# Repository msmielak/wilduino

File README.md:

# wilduino
Arduino-based, open-source animal-borne logger

Copyright (C) 2016  Michał Śmielak

    This program is free software: you can redistribute it and/or modify
    it under the terms of the GNU General Public License as published by
    the Free Software Foundation, either version 3 of the License, or
    (at your option) any later version.

    This program is distributed in the hope that it will be useful,
    but WITHOUT ANY WARRANTY; without even the implied warranty of
    MERCHANTABILITY or FITNESS FOR A PARTICULAR PURPOSE.  See the
    GNU General Public License for more details.

    You should have received a copy of the GNU General Public License
    along with this program.  If not, see <http://www.gnu.org/licenses/>.

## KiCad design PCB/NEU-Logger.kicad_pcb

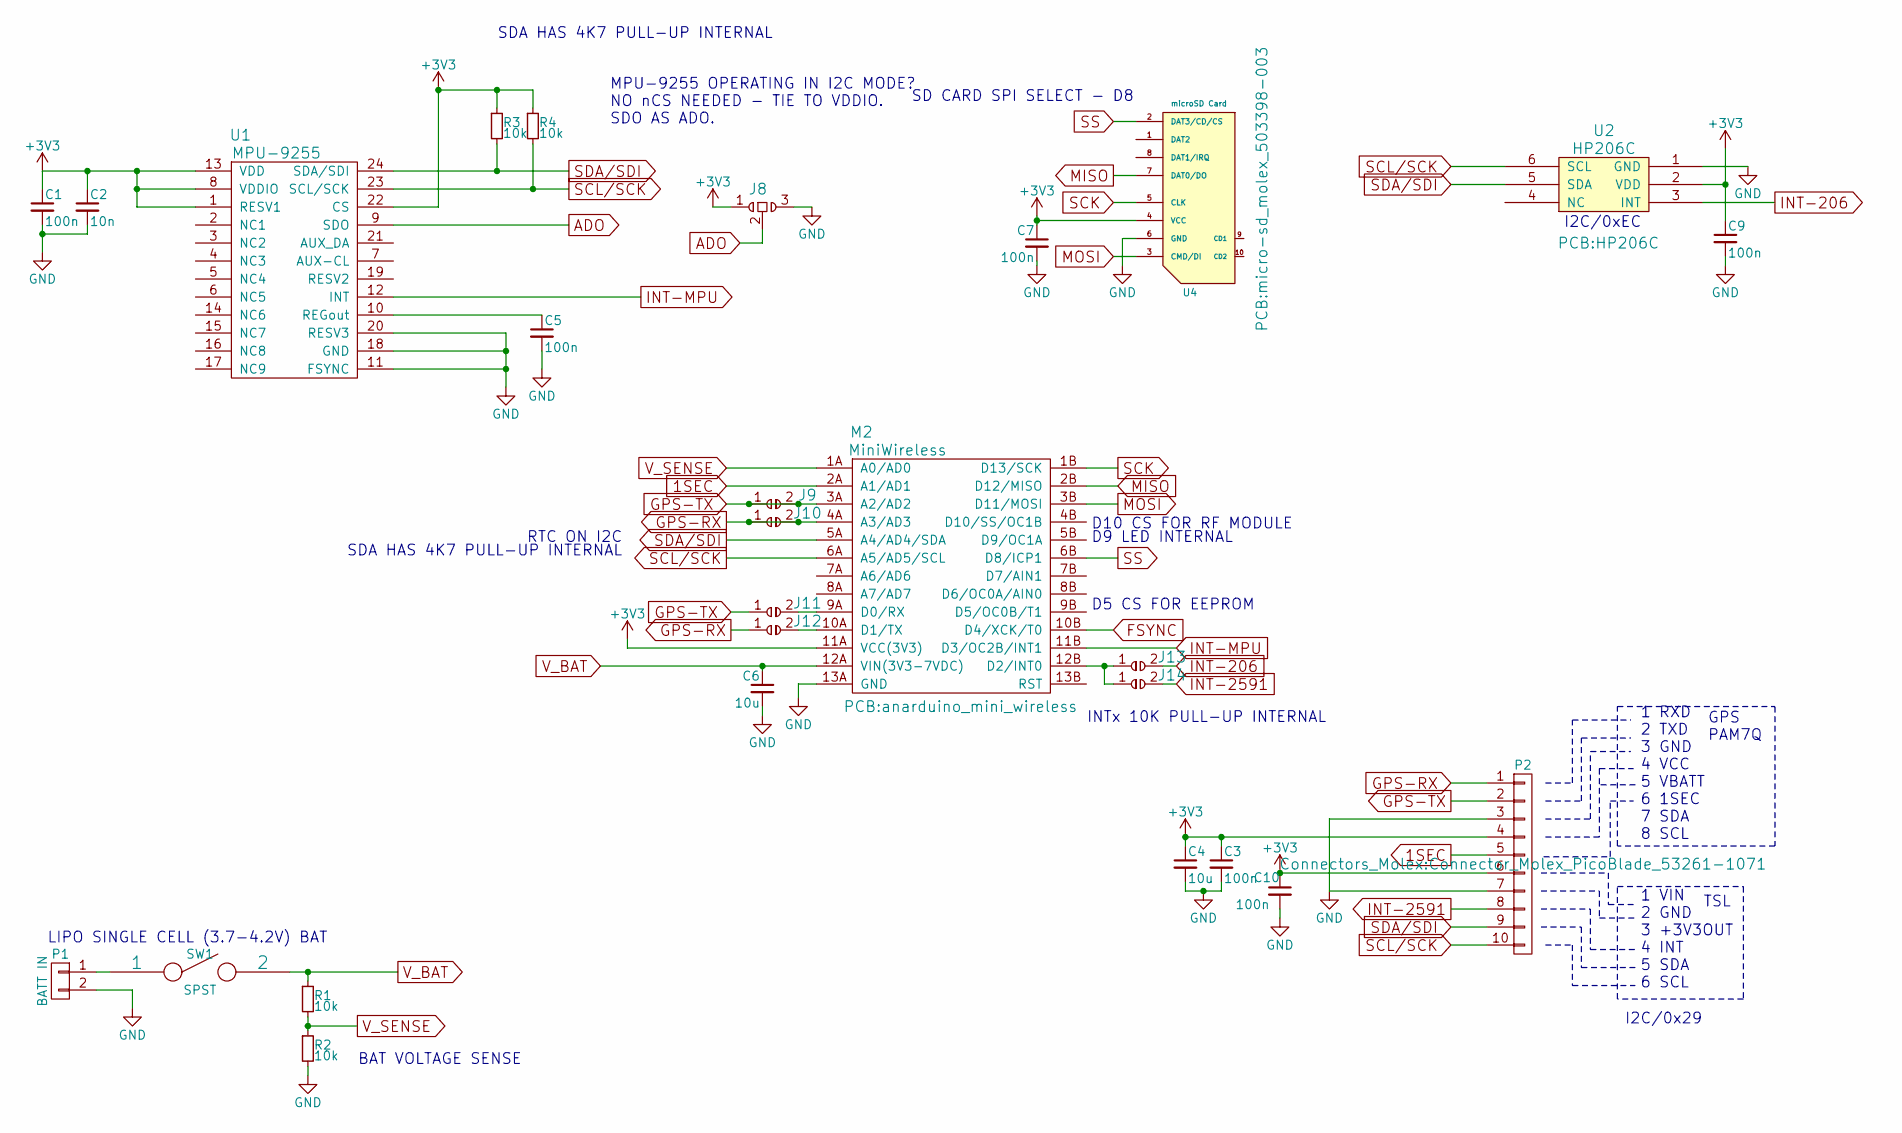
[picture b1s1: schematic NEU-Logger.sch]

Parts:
C1, C5: 100n; C_0603
C2: 10n; C_0603
C3, C7, C9, C10: 100n; C_0603_HandSoldering
C4, C6: 10u; C_0603_HandSoldering
J8: SOLDERJUMPER-CO; SolderJumper_3
J9, J10, J11, J12, J13, J14: SOLDERJUMPER; SolderJumper_2
M2: MiniWireless; anarduino_mini_wireless
P1: BATT IN; Pin_Header_Straight_1x02; Part B2B-PH-K-S(LF)(SN)
P2: CONN_01X10; Connector_Molex_PicoBlade_53261-1071
R1, R2: 10k; R_0603_HandSoldering
R3, R4: 10k; R_0603
SW1: SPST; reed_switch_glass_14mm; Part MK24-B-3-OE
U1: MPU-9255; QFN-24-1EP_3x3mm_Pitch0.4mm
U2: HP206C
U4: microSD Card; micro-sd_molex_503398-003; Part SD-503398-003

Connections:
1SEC: M2.2A (A1/AD1), P2.5
+3V3: C1.1, C2.1, C3.1, C4.1, C7.1, C9.1, C10.1, J8.1, M2.11A (VCC(3V3)), P2.4, P2.6, R3.1, R4.1, U1.1 (RESV1), U1.8 (VDDIO), U1.13 (VDD), U1.22 (CS), U2.2 (VDD), U4.4 (VCC)
ADO: J8.2, U1.9 (SDO)
GND: C1.2, C2.2, C3.2, C4.2, C5.2, C6.2, C7.2, C9.2, C10.2, J8.3, M2.13A (GND), P1.2, P2.3, P2.7, R2.2, U1.11 (FSYNC), U1.18 (GND), U1.20 (RESV3), U2.1 (GND), U4.6 (GND)
GPS-RX: J10.1, J10.2, J12.1, M2.4A (A3/AD3), P2.1
GPS-TX: J9.1, J9.2, J11.1, M2.3A (A2/AD2), P2.2
INT-206: J13.2, U2.3 (INT)
INT-2591: J14.2, P2.8
INT-MPU: M2.11B (D3/OC2B/INT1), U1.12 (INT)
MISO: M2.2B (D12/MISO), U4.7 (DAT0/DO)
MOSI: M2.3B (D11/MOSI), U4.3 (CMD/DI)
unnamed: C5.1, U1.10 (REGout)
unnamed: J11.2, M2.9A (D0/RX)
unnamed: J12.2, M2.10A (D1/TX)
unnamed: J13.1, J14.1, M2.12B (D2/INT0)
unnamed: P1.1, SW1.1
SCK: M2.1B (D13/SCK), U4.5 (CLK)
SCL/SCK: M2.6A (A5/AD5/SCL), P2.10, R4.2, U1.23 (SCL/SCK), U2.6 (SCL)
SDA/SDI: M2.5A (A4/AD4/SDA), P2.9, R3.2, U1.24 (SDA/SDI), U2.5 (SDA)
SS: M2.6B (D8/ICP1), U4.2 (DAT3/CD/CS)
V_BAT: C6.1, M2.12A (VIN(3V3-7VDC)), R1.1, SW1.2
V_SENSE: M2.1A (A0/AD0), R1.2, R2.1

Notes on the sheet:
I2C/0x29
I2C/0xEC
MPU-9255 OPERATING IN I2C MODE? NO nCS NEEDED - TIE TO VDDIO. SDO AS ADO.
LIPO SINGLE CELL (3.7-4.2V) BAT
D10 CS FOR RF MODULE
RTC ON I2C
D5 CS FOR EEPROM
SDA HAS 4K7 PULL-UP INTERNAL
INTx 10K PULL-UP INTERNAL
D9 LED INTERNAL
BAT VOLTAGE SENSE
SD CARD SPI SELECT - D8
1 RXD 2 TXD 3 GND 4 VCC 5 VBATT 6 1SEC 7 SDA 8 SCL
1 VIN 2 GND 3 +3V3OUT 4 INT 5 SDA 6 SCL
GPS PAM7Q
TSL

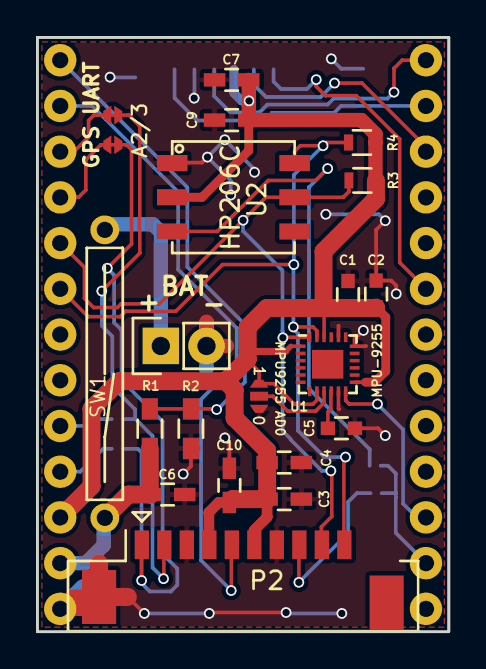
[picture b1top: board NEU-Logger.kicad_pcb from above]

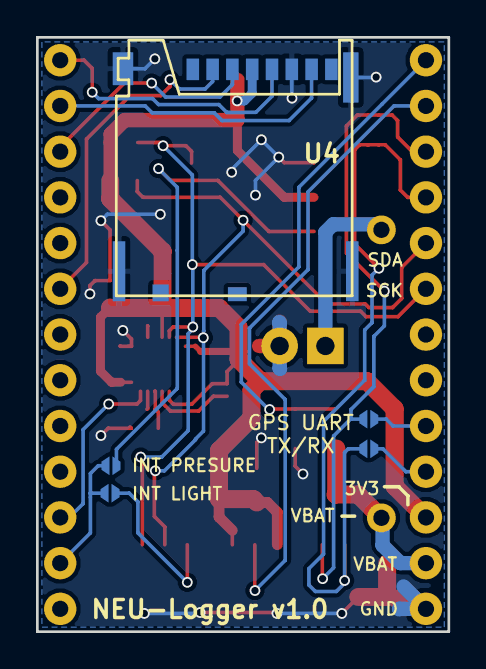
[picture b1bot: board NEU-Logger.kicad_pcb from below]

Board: 2 copper layers, 22.9 x 33.0 mm, 27 parts (5 on the bottom side), 22 nets.

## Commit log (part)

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2016-08-09 Create main_routine
2016-08-11 PCB files added
    Logger PBC design files added (Kicad format)
2016-08-11 First UBlox GPS code added
    This is just a general UBlox code from arduino playground
    (http://playground.arduino.cc/UBlox/GPS)
2016-08-11 PCB files added
    Kicad design files for the sensor shield
2017-04-05 HP206C barometric sensor datasheet and library
2017-04-05 Test script for the HP206C barometric sensor
2017-04-05 minor revisions in HP206C code
2017-04-05 RTC library
2017-05-19 Main script
    Adding main script to the GitHub for future development
2017-05-23 Now saves to one file. Comments updated. Bug fixed. Reformatted.
2017-05-25 Bug fixed. setSleep[] now automatically populated with SLEEPFOR value. Replaced LowPower library with Narcoleptic
2017-05-29 Changes to include power saving and blinking
    Added 2 libraries to manage (turn off) flash memory and radio module. Also added some blinking code to make it easier to monitor logger when not plugged into computer.
2017-05-29 Inlcuding to do list to have all the coments in one place
2017-05-29 commented out radio module and flash memory code
    with these 2 libraries and 3 lines of code the GPS would not initialise. I assume there wasn't enough memory left for local variables.
2017-05-29 Concept for GPS logging part
2017-06-01 Power management changes
    Added simple power consumption test to test sleep power consumption of all the onboard sensors (low_power_test.ino) and included short code to disable the accelerometer in main code
2020-12-29 cleaning up
